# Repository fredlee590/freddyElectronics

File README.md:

freddyElectronics
=================

Repository to keep up with hobbyist electronics projects

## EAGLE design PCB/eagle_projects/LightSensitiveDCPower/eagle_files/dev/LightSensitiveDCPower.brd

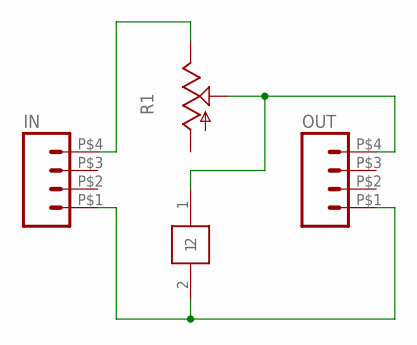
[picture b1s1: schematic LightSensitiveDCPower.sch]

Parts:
IN: M04HORIZ_PTH; SULLIN-1X4_HORIZ
OUT: M04HORIZ_PTH; SULLIN-1X4_HORIZ
PC1: PDV-P8101; PHOTOCELL_CERAMIC
R1: TRIM_US-B25P; B25P

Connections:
unnamed: IN.P$1 (1), OUT.P$1 (1), PC1.2
unnamed: IN.P$4 (4), R1.E
unnamed: OUT.P$4 (4), PC1.1, R1.S

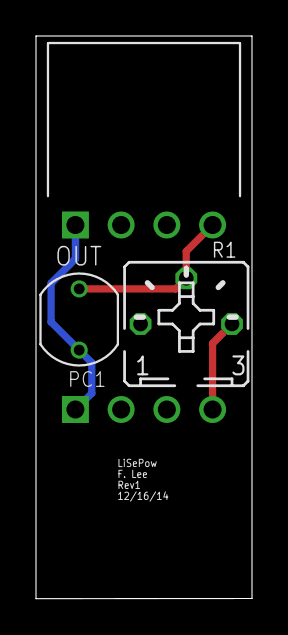
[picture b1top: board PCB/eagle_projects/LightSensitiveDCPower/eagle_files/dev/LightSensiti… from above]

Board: 2 copper layers, 12.0 x 31.3 mm, 4 parts (1 on the bottom side), 3 nets.

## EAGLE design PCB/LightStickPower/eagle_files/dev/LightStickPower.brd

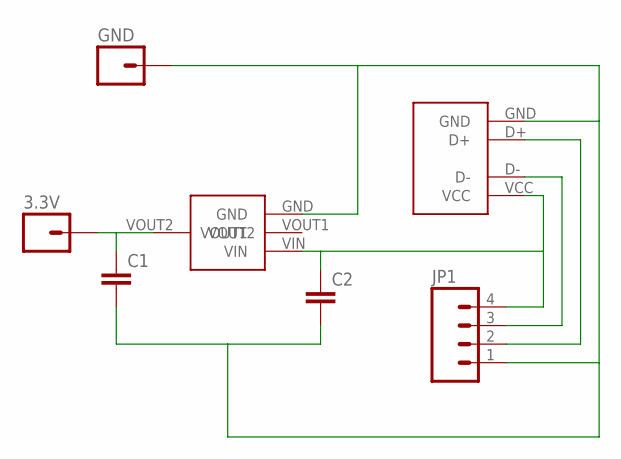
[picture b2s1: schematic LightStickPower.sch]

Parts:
3.3V: M01PTH; 1X01
C1, C2: CAP0805; 0805
GND: M01PTH; 1X01
JP1: M04PTH; 1X04
USB1: USB_A_932
V1: VOLTAGE_REGULATOR_AP2114H; SOT-223

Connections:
unnamed: C2.1, JP1.4, USB1.VCC, V1.VIN
unnamed: JP1.3, USB1.D-
unnamed: JP1.2, USB1.D+
unnamed: C1.2, C2.2, GND.1, JP1.1, USB1.GND, V1.GND
unnamed: 3.3V.1, C1.1, V1.VOUT2

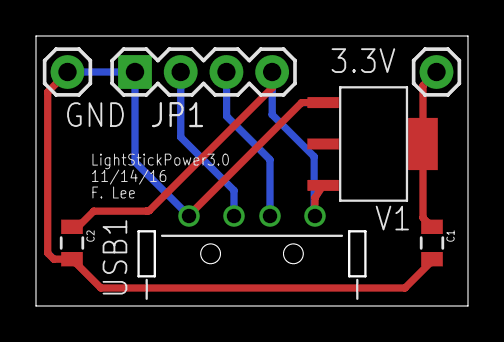
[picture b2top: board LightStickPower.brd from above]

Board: 2 copper layers, 23.9 x 14.9 mm, 7 parts (0 on the bottom side), 5 nets.

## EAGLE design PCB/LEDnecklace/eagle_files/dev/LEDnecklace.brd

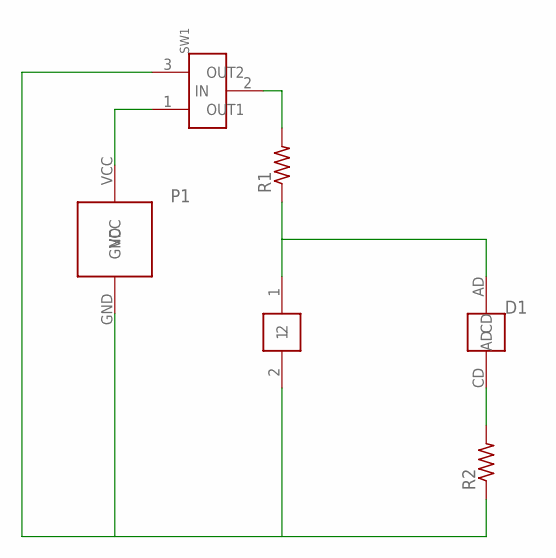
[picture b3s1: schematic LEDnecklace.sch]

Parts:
D1: XLAMP_XBD
P1: BC501SM_BATT_HOLD
PC1: PDV-P8101; PHOTOCELL_CERAMIC
R1, R2: R-US_R0603; R0603
SW1: PCM12SMTR

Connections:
unnamed: R1.2, SW1.2 (IN)
unnamed: P1.GND, PC1.2, R2.1, SW1.3 (OUT2)
unnamed: P1.VCC, SW1.1 (OUT1)
unnamed: D1.AD, PC1.1, R1.1
unnamed: D1.CD, R2.2

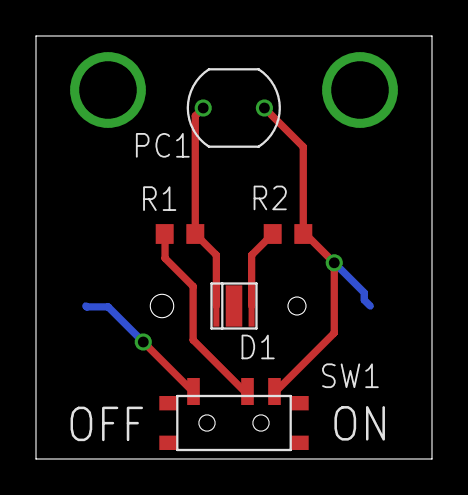
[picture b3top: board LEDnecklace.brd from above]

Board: 2 copper layers, 22.0 x 23.5 mm, 6 parts (1 on the bottom side), 5 nets.

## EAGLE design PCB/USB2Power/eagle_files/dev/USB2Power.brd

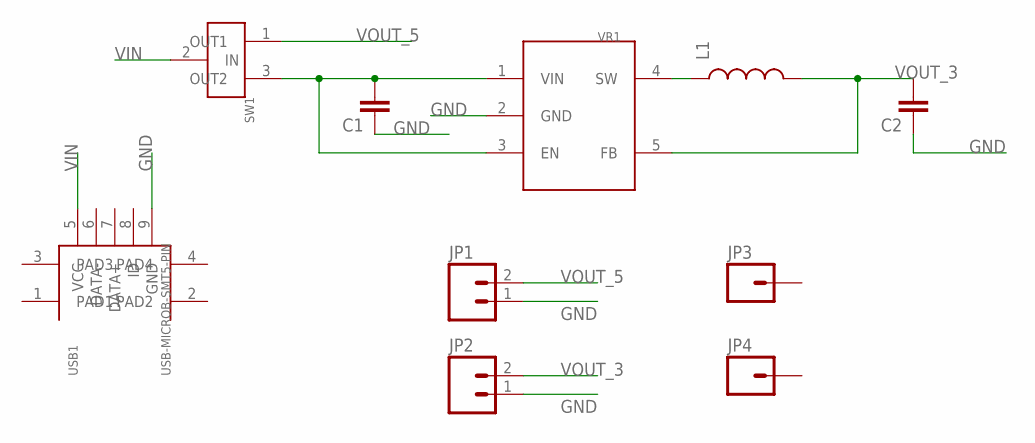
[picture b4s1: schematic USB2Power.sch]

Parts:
C1, C2: CAP0603-CAP; 0603-CAP
JP1, JP2: M02PTH; 1X02
JP3, JP4: M01PTH; 1X01
L1: INDUCTOR30OHM,1.8A; 0603
SW1: PCM12SMTR
USB1: USB-MICROB-SMT5-PIN; USB-MICROB-SMT
VR1: ADP2108; UJ-5_TSOT

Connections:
GND: C1.1, C2.1, JP1.1, JP2.1, JP3.1, JP4.1, USB1.9 (GND), VR1.2 (GND)
unnamed: C1.2, SW1.3 (OUT2), VR1.1 (VIN), VR1.3 (EN)
unnamed: L1.1, VR1.4 (SW)
VIN: SW1.2 (IN), USB1.5 (VCC)
VOUT_3: C2.2, JP2.2, L1.2, VR1.5 (FB)
VOUT_5: JP1.2, SW1.1 (OUT1)

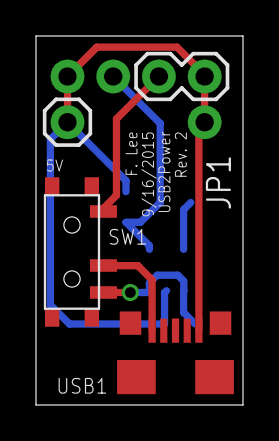
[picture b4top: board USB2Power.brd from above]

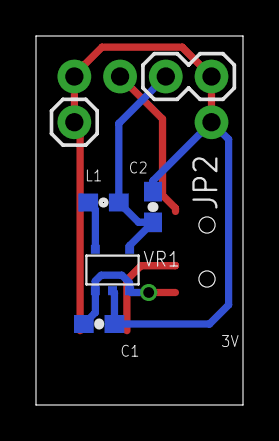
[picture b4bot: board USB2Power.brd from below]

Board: 2 copper layers, 11.5 x 20.5 mm, 10 parts (6 on the bottom side), 6 nets.

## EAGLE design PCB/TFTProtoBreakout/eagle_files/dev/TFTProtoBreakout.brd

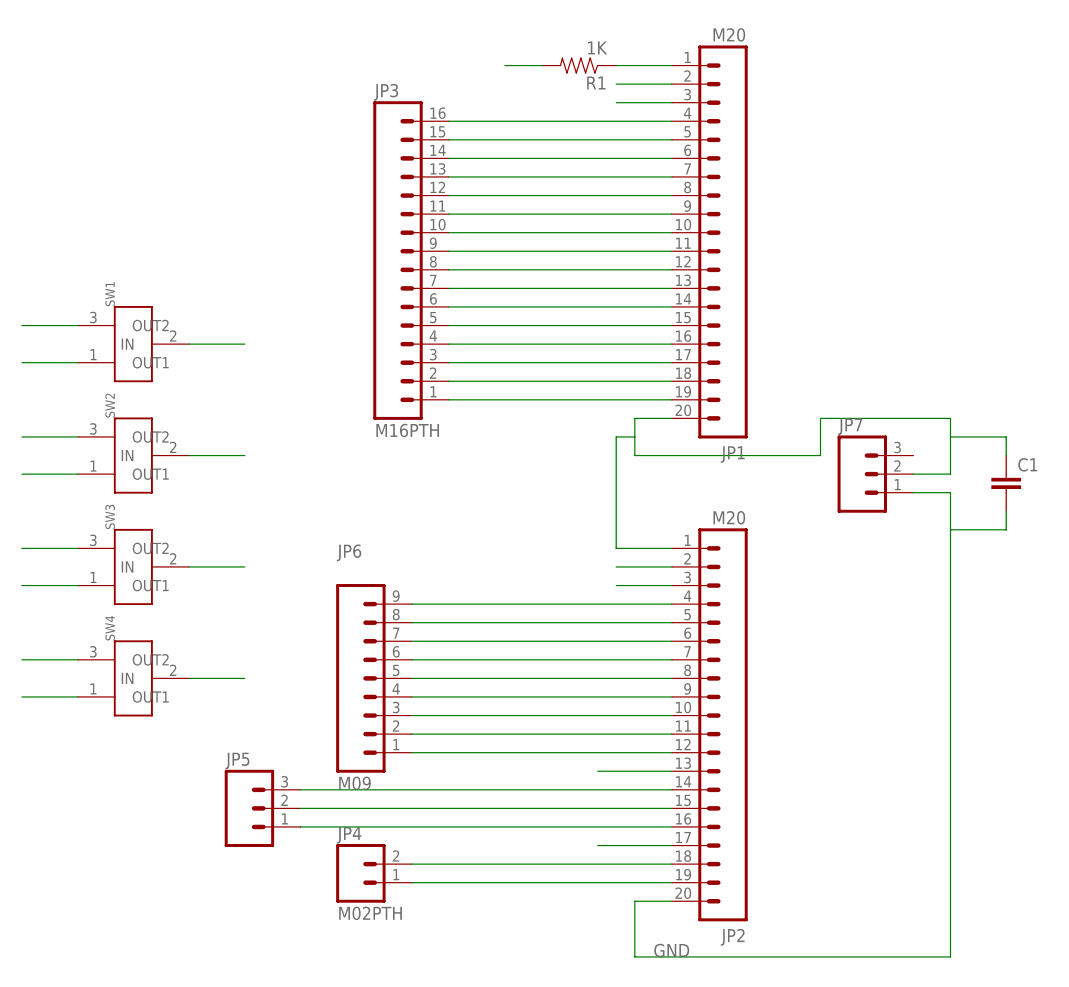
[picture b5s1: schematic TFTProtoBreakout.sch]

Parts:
C1: CAP0805; 0805
JP1, JP2: M20; 1X20
JP3: M16PTH; 1X16
JP4: M02PTH; 1X02
JP5, JP7: M03PTH; 1X03
JP6: M09; 1X09
R1: 1K; 0603-RES
SW1, SW2, SW3, SW4: PCM12SMTR

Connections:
D0: JP1.13, JP3.7
D1: JP2.12, JP6.1
D2: JP1.12, JP3.8
D3: JP2.11, JP6.2
D4: JP1.11, JP3.9
D5: JP2.10, JP6.3
D6: JP1.10, JP3.10
D7: JP2.9, JP6.4
D8: JP1.9, JP3.11
D9: JP2.8, JP6.5
D10: JP1.8, JP3.12
D11: JP2.7, JP6.6
D12: JP1.7, JP3.13
D13: JP2.6, JP6.7
D14: JP1.6, JP3.14
D15: JP2.5, JP6.8
D16: JP1.5, JP3.15
D17: JP2.4, JP6.9
FMARK: JP1.17, JP3.3
GND: C1.2, JP2.13, JP2.17, JP2.20, JP7.1, R1.2, SW1.1 (OUT1), SW2.1 (OUT1), SW3.1 (OUT1), SW4.1 (OUT1)
IM0: JP1.2, SW1.2 (IN)
IM1: JP2.2, SW2.2 (IN)
IM2: JP1.3, SW3.2 (IN)
IM3: JP2.3, SW4.2 (IN)
LEDK: JP1.1, R1.1
NCS: JP2.16, JP5.1
NRD: JP1.15, JP3.5
NRST: JP1.4, JP3.16
NWR_SCL: JP2.15, JP5.2
RS: JP1.16, JP3.4
SDI: JP2.14, JP5.3
SDO: JP1.14, JP3.6
VCC: C1.1, JP1.20, JP2.1, JP7.2, SW1.3 (OUT2), SW2.3 (OUT2), SW3.3 (OUT2), SW4.3 (OUT2)
X+: JP1.18, JP3.2
X-: JP1.19, JP3.1
Y+: JP2.18, JP4.2
Y-: JP2.19, JP4.1

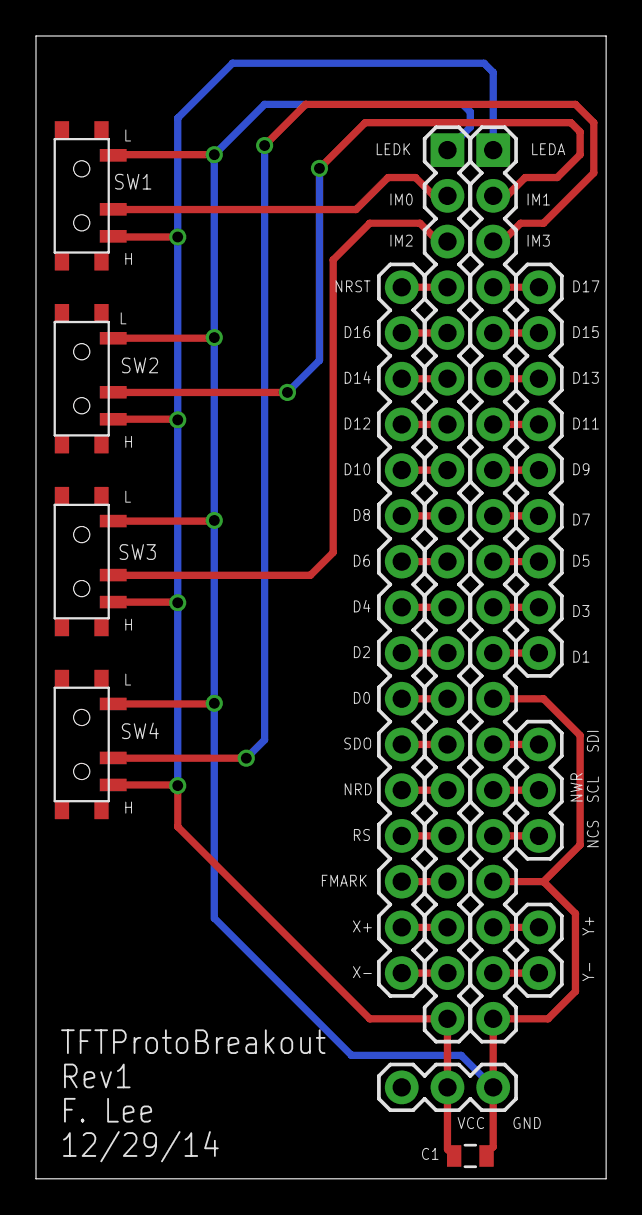
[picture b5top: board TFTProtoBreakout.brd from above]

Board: 2 copper layers, 31.7 x 63.5 mm, 13 parts (1 on the bottom side), 37 nets.

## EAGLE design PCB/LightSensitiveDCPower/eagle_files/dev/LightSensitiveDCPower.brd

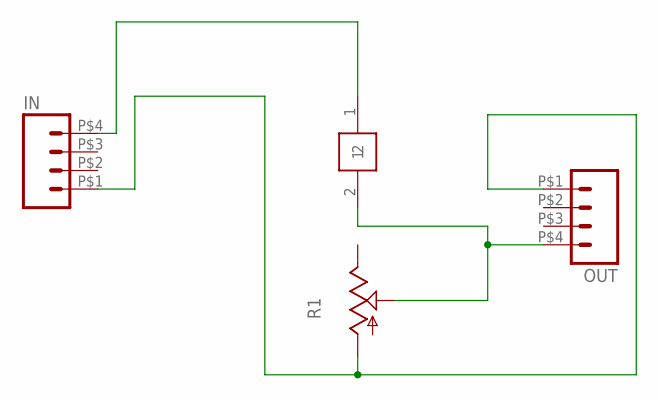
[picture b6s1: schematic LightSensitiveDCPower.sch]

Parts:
IN: M04HORIZ_PTH; SULLIN-1X4_HORIZ
OUT: M04HORIZ_PTH; SULLIN-1X4_HORIZ
PC1: PDV-P8101; PHOTOCELL_CERAMIC
R1: TRIM_US-B25P; B25P

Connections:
unnamed: IN.P$1 (1), OUT.P$1 (1), R1.A
unnamed: IN.P$4 (4), PC1.1
unnamed: OUT.P$4 (4), PC1.2, R1.S

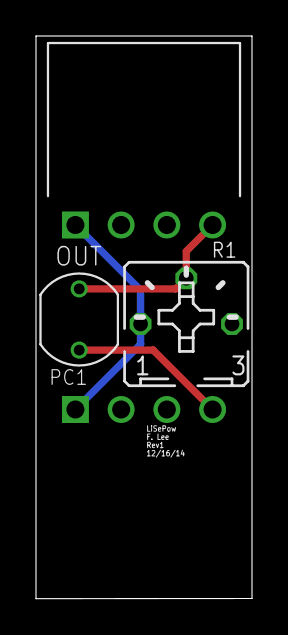
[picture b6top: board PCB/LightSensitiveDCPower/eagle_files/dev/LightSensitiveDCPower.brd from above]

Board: 2 copper layers, 12.0 x 31.3 mm, 4 parts (1 on the bottom side), 3 nets.

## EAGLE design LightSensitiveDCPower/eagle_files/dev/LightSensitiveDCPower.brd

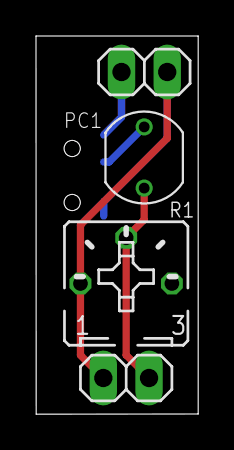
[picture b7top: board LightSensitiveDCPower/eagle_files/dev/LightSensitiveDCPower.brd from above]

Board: 2 copper layers, 9.0 x 21.0 mm, 5 parts (1 on the bottom side), 4 nets.

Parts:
IN: 1X02
OUT: 1X02
PC1: PHOTOCELL_CERAMIC
R1: B25P
SW1: PCM12SMTR

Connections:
unnamed: IN.1, OUT.1, R1.A, SW1.1
unnamed: IN.2, SW1.3
unnamed: PC1.1, SW1.2
unnamed: OUT.2, PC1.2, R1.S

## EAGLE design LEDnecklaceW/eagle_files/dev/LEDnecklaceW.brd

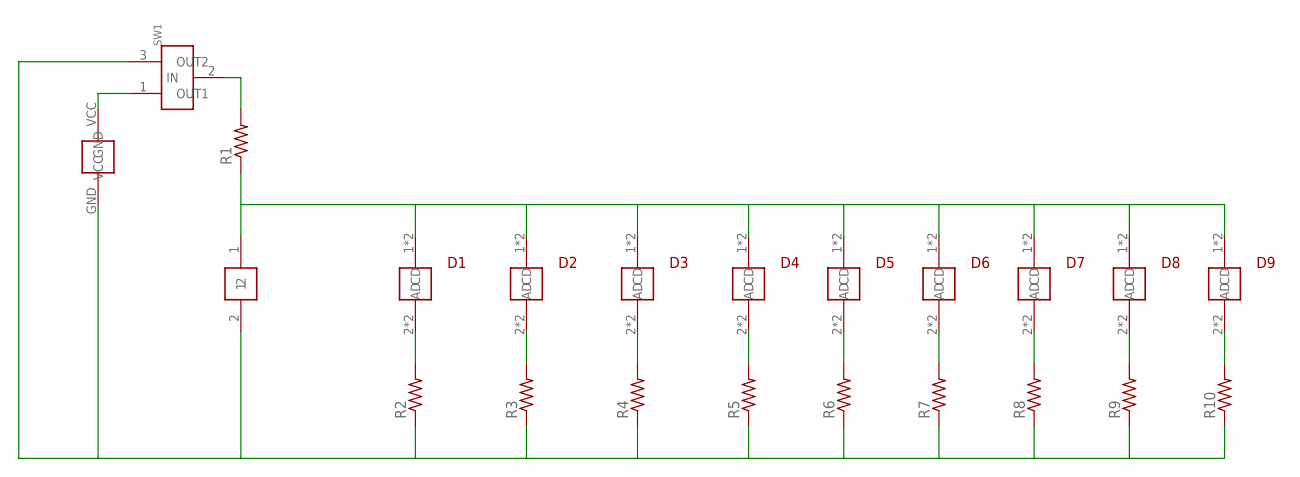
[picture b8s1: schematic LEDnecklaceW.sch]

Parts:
D1, D2, D3, D4, D5, D6, D7, D8, D9: SZA05A0A
P1: BU2032SM-BT-GCT; SMD_BATT_HOLDER_2032
PC1: PDV-P8101; PHOTOCELL_CERAMIC
R1, R2, R3, R4, R5, R6, R7, R8, R9, R10: R-US_R0603; R0603
SW1: PCM12SMTR

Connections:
unnamed: R1.2, SW1.2 (IN)
unnamed: P1.GND, PC1.2, R2.1, R3.1, R4.1, R5.1, R6.1, R7.1, R8.1, R9.1, R10.1, SW1.3 (OUT2)
unnamed: D1.2 (CD), D1.12 (CD), R2.2
unnamed: P1.VCC, SW1.1 (OUT1)
unnamed: D2.2 (CD), D2.12 (CD), R3.2
unnamed: D3.2 (CD), D3.12 (CD), R4.2
unnamed: D4.2 (CD), D4.12 (CD), R5.2
unnamed: D5.2 (CD), D5.12 (CD), R6.2
unnamed: D6.2 (CD), D6.12 (CD), R7.2
unnamed: D7.2 (CD), D7.12 (CD), R8.2
unnamed: D8.2 (CD), D8.12 (CD), R9.2
unnamed: D9.2 (CD), D9.12 (CD), R10.2
unnamed: D1.1 (AD), D1.11 (AD), D2.1 (AD), D2.11 (AD), D3.1 (AD), D3.11 (AD), D4.1 (AD), D4.11 (AD), D5.1 (AD), D5.11 (AD), D6.1 (AD), D6.11 (AD), D7.1 (AD), D7.11 (AD), D8.1 (AD), D8.11 (AD), D9.1 (AD), D9.11 (AD), PC1.1, R1.1

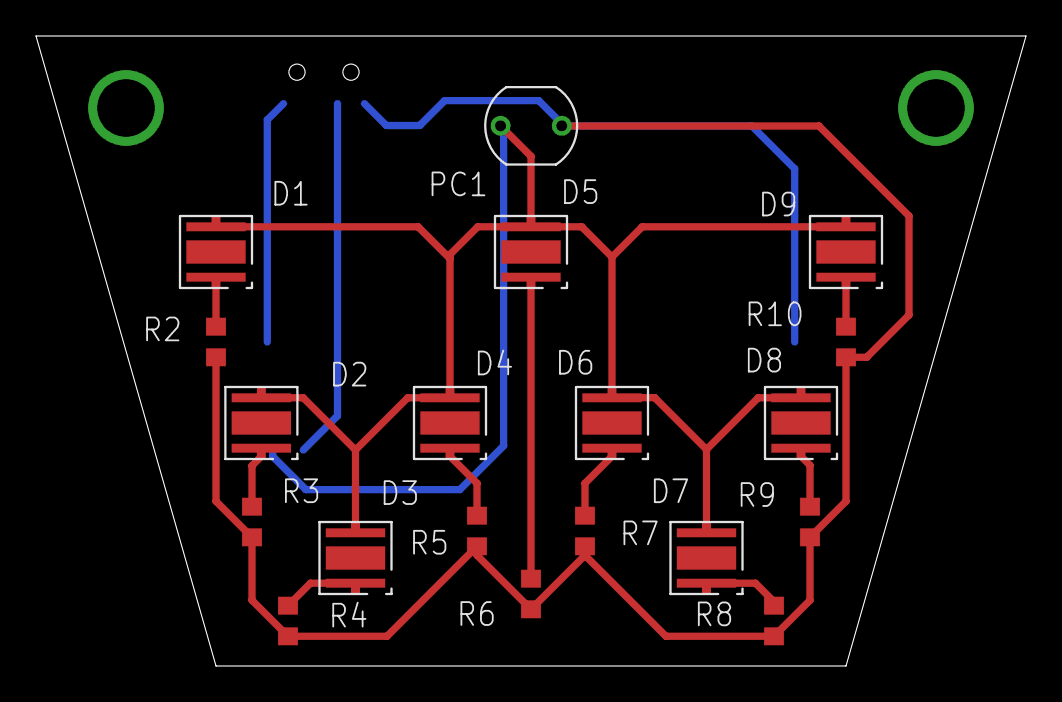
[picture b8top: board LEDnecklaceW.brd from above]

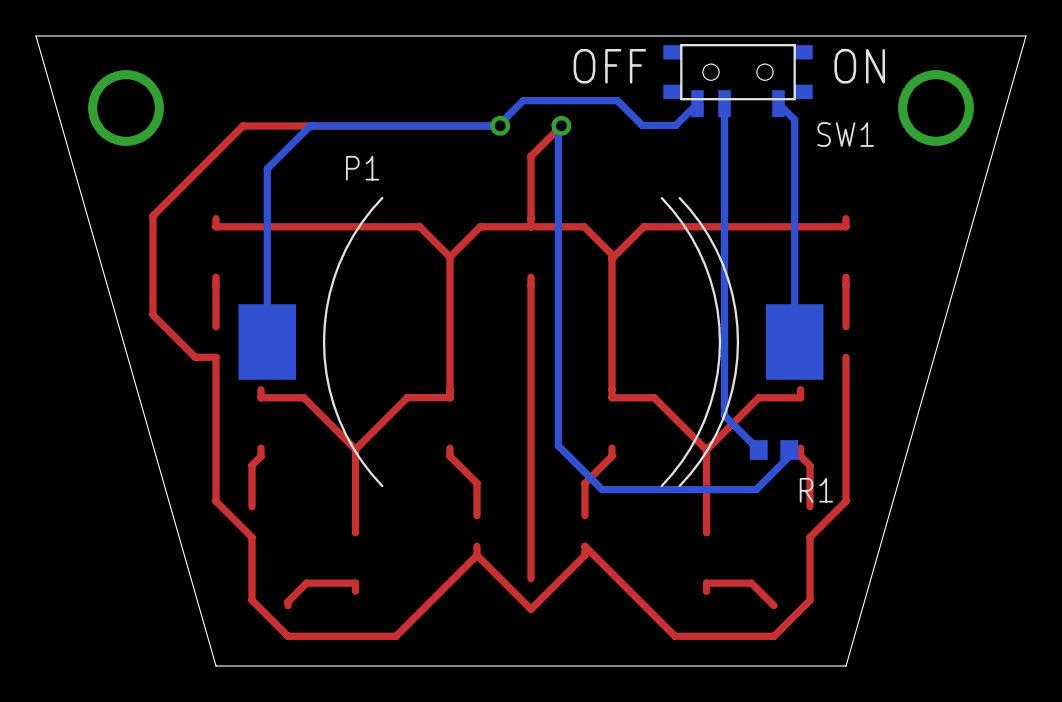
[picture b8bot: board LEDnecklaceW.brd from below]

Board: 2 copper layers, 55.0 x 35.0 mm, 22 parts (3 on the bottom side), 13 nets.

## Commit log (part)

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2013-08-07 new project folder and initial file in the form of a partlist
2013-08-18 add eagle files. checkpoint. have functional set board lay out. attempting to consolidate
2013-08-18 add script file to copy select eagle files (project, schematic, and board) into dev folder
2013-08-18 new file structure to prepare for later projects. copy_eagle modified to correpsond to new files structure.
2013-08-18 copy_eagle added to commit list
2013-08-18 new consolidated mcuPower.brd
2013-08-19 updated eagle project and board and generated gerber files. modified copy_eagle to get output as well
2013-08-26 most complete to date files
2013-08-26 added mcuPower.dri as aperture wheel file and committed associated changes
2013-08-26 added dxf file and edited copy_eagle to copy this as well
2013-08-31 tweaked voltage regulator to remove some silkscreen guide lines that overlap with traces
2013-09-02 packaged eagle_files into zip folder for easy emailing
2013-09-02 moved some files around. better name for eagle_files.zip and more organized location for mcuPower.xls
2013-09-02 deleted mcuPower.xls as part of previous commit
2013-09-02 zip file is now a subset of previous. only production files
2013-09-08 various changes + production files. Reroutes, library footprint changes, and moving pot to front side of board
2013-09-22 added GML file for board outline for Seeedstudio. Modified copy_eagle script to include GML. Peripheral changes to eagle.epf and mcuPower.dri
2013-09-22 Rename zips with production files
2013-09-22 move mcuPower_prod_proto.zip \(renamed\) to mcuPower directory
2013-09-22 Making official the deletion of mcu_prod_proto.zip
2013-10-26 removed label in silkscreen for stabilizing pin
2013-10-27 new production files for OSHPark. also, copy_eagle version to copy those files to the production file folder. board design itself shows flipped coin battery holder
2013-10-27 corrected naming of Gerber for top layer and bottom layer
2013-10-27 adding zip file for OSHPark's specifications
2013-12-23 initial commit of mcuWallPower project: A variation of mcuPower that delivers power to a breadboard from a single coin battery or a micro-B USB cable.
2013-12-24 Added USB mini connector to board along with other components. Todo: Replace USB mini connector with USB micro B connector. Looks like I'll need to make a custom footprint.
2013-12-24 renamed copy_eagle to copy_eagle.sh. More professional convention (?).
2013-12-26 add eagle library to git. contains handful of custom parts.
2013-12-26 mcuWallPower schematic and board updated. Ready for fitting.
2014-01-06 latest project files. using latest footprint for USB-micro-B component.
2014-01-06 initial commit for LED necklace BOM
2014-01-12 generated top and bottom overlay (silkscreens) with PCB info changed from top to bottom silkscreen.
2014-01-12 updated board file to put ID information on the back.
2014-01-19 Renamed BOM_LED_Necklace.xlsx to BOM_LED_Necklace.xls
2014-01-19 Adjust last entry to include single purchase option.
2014-01-20 Final candidate list of LEDs
2014-01-20 update spreadsheet to reflect datasheets.
2014-01-20 upload datasheets thus far.
2014-01-27 copy_eagle.sh assigns project name at the beginning. more versatile for future revision. also creates project folder if not already present.
2014-01-27 initial commit of LEDtestBoard PCB project . Power finalized, switches and LEDs in general place. Set up for one side to hold 4 LEDs and the other to hold a multicolored LED, controlled with 4 switch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
2014-02-02 added two new datasheets to match previous commit of new LEDs (including multicolored LED).
2014-02-02 Formalized decisions on 5 LEDs to use
2014-02-02 Added gull wing LED (already have) to list
2014-02-02 added datasheet for the photocell to use
2014-02-02 Updated BOM spreadsheet for photocell.
2014-02-13 add test to test merge one file
2014-02-13 more test.txt
2014-02-15 Add datasheet for amber version of last LED
2014-02-15 Update BOM to use all amber LEDs. Also narrow down search to two
2014-02-17 Updated LEDtestBoard dev files. Ready to begin pad check and routing.
2014-02-21 Placed components in approximately precise locations. Ready to begin routing.
2014-02-21 Modified LED footprints to have more visible special corner and to display names.
2014-02-26 All routed.
2014-03-06 New design rules and all visible. And some other stuff. Project files.
2014-03-06 Add production files. Getting ready to request.
2014-03-09 Adjusted part labels in board design and generated output accordingly.
2014-03-10 All layers visible
2014-03-10 Move components around to make USB micro B power source more stable. Coin battery upright.
2014-03-10 Output files of mcuWallPower version 2. Switch sources with output positions.
2014-03-10 Move text under trace. Just in case heating concern.
2014-04-05 Remove dxf file for mcuWallPower. Not needed for OSHPark.
2014-04-05 LEDnecklaceW board routed.
2014-04-05 LEDnecklaceW board and schematic updated to show component names for photocell and battery.
2014-04-05 Updated freddyLibr.lbr - Show names of photocell and battery case.
2014-04-05 Moved some names around.
2014-04-05 First run of Eagle production files for OSHPark.
2014-04-06 Added switch to board and schematic. Also added output production files corresponding to these changes.
2014-04-06 Added labels for ON and OFF position. board and changed production files.
2014-04-10 updated eagle production files for final submission
2014-07-26 Add GML (outline) and TXT (Drill Drawing) to match SeeedStudio requirements.
2014-08-19 Add BOM for convenient part ordering
2014-08-19 Added part spaces.
2014-09-20 Create new project LightSensitiveDCPower
2014-09-20 Re-place parts with readjusted text and new labels
2014-09-20 Further rearranging and resizing.
2014-09-20 Corrected Pot miswiring. Further rearranging and resizing. I think this is it.
2014-09-20 Restructuring of project file. Apparently.
2014-09-20 Add LightSensitiveDCPower production files.
2014-09-25 Minor changes due to regeneration of production files.
2014-09-25 Elongate board to save for wiidth. Check point.
2014-11-24 Move all PCB files to new PCB directory. Update Bill of Materials for LEDnecklaceW.
2014-12-02 New horizontal female header scheme for Light Sensitive DC power with dimensions adjusted accordingly.
2014-12-03 Rearranged components so that board is less long.
2014-12-03 Routed and produced production files.
2014-12-03 Yet another tweaking of component postiions.
2014-12-13 Removed switch. Intended use case turned out to be out of rating.
2014-12-13 Initial check in of BeagleBone Black robotic stuff.
2014-12-15 Changed board label to Rev1 and today.
2014-12-15 Bring PCB label into soldermask
2014-12-15 Files generated by new CAM file.
2014-12-28 Added first cut of trace routing to board design. A bit messy, but functional.
2014-12-28 Modified to be a bit more clean.
2014-12-28 Added pin labels and rerouted to work around these a bit more cleanly. Also included note about switch todo.
2014-12-29 Minor changes to eagle project file.
2014-12-29 Laid switches on one face abreast and routed.
2014-12-29 Finalize routing to be more clean. Add keyhole for Power connections and Add labels.
2014-12-30 Rename label to TFTProtoBreakout.
2014-12-30 Eagle project file changed after save. Different position?
2015-01-11 LiSensiPow actually works now
2015-08-18 Add 5V to 3.3V voltage regulator to freddy library.
2015-08-18 Add schematic and board file for USB2Power project. First cut of component placement.
2015-08-21 USB2Power board components placed and ready for routing.
2015-08-21 Slightly tweak borders of USB2Power.
2015-08-21 All connected up. Also added ground for the other two header pins as opposed to NC. Made connections a little better. Some known DRC failures.
2015-08-21 Add OSHPark's design rules file.
2015-08-25 Resolve DRC conflicts with USB2Power.brd
2015-08-25 Add Board descriptor.
2015-08-26 First generation of production files.
2015-09-15 Add separate headers for 5V and 3V power outputs. Joint header + inductor may have been causing problems.
2015-09-25 Add basic serial PIC project as a starting point for projects with debugging.
2015-09-25 Move basic project to platform specific folder 18F24J50
2015-09-26 Turn off watchdog timer.
2015-09-26 Remove build files.
2015-09-29 Include starting position of RF transmitter and receiver.
2015-10-29 Snapshot of RFtransmitter with basic read from RF module.
2015-11-05 Move project to Git directory.
2015-11-05 Basic SPI scaffolding.
2015-11-05 Snapshot before major surgery.
2015-11-05 Adjusted readReg and writeReg functions to return success (0) or error code (-1).
2015-11-17 Compress function to get STATUS register and unify function to write SPI.
2015-11-18 Fix up readStatus function and add write checks in debugging capacity.
2015-11-18 Miscellaneous clean up via more macros. First attempt to send a packet.
2015-11-18 Minor tweaks to process to try to get TX interrupt to fire. Command for write that doesn't require an ACK. More Nops. Disable sending external interrupt notification.
2015-11-25 Add quintessential blinking project. Useful for experimenting with delays.
2015-11-25 Refactor config write function to be more direct.
2015-12-04 Further attempts to transmit packet. Move configuration around, add function to flush TX FIFO, extra checks.
2015-12-09 Refactor function structure to match example code.
2016-03-23 First cut of LED test necklace's Eagle dev files.
2016-03-24 Add Digikey order for LEDs etc.
2016-03-25 Add new generation of datasheets.
2016-03-25 Rename datasheets to make them easier to identify.
2016-03-28 Add new LED XLamp XB D to library and simple breakout board.
2016-03-30 Develop version of LEDnecklace with XLampXBD and smaller coin cell (type 2016).
2016-03-30 Price analysis for LEDnecklace.
2016-05-18 Change border around LED. Hopefully more visible.
2016-06-28 Add Arduino projects with first submission. Light sock design document.
2016-07-06 Add 3D printing directory along with first project: RouterRack.
2016-07-06 Updated FCStd files. Somehow.
2016-08-12 Initial check-in of LightStickPower and associated updated freddyLibr.lbr
2016-08-15 Finalize LightStickPower.
2016-08-19 Initial commit of some test code (midpoint to production code) and hardware design documentation.
2016-08-23 Add drawing for core of LightStick. To be laser cut from polycarbonate sheet.
2016-08-23 Update routerRack development and production files.
2016-08-23 Initial check in of Light Stick block diagram.
2016-08-24 Widen USB micro slot. Developer and production file.
2016-08-25 Initial check in of short router rack side.
2016-08-25 Add crossbar for stability.
2016-08-25 Adjusted line segment names.
2016-08-26 Add back stabilizer piece.
2016-08-29 Adjust core drawing to have holes and smaller dimensions.
2016-09-20 Update LightStickPower with more precise borders and thinner traces where appropriate.
2016-09-20 Add holes to allow for pins on prototype Teensy and accelerometer.
2016-09-20 Adjust short router rack pieces to be just a little bit bigger. Bet I got it this time.
2016-09-20 Updated date on LightStickPower.
2016-09-20 Narrow board to fit in tube.
2016-10-04 Updated core.
2016-10-04 Adjust USB micro B head of LightStickPower.
2016-10-08 Removed extraneous line.
2016-11-15 Updated Light stick power to use cabled USB-micro-B plug. Also commit properly pathed copy_eagle. Getting annoying.
2016-11-28 Add crystalPerch, a stand for crystal acquired in Japan.
2016-11-28 Reset view for crystalPerch. Remove extraneous file.
2016-11-28 Remove extraneous sketch.
2016-12-26 Add accessory holes. Power and photoresistor.
2016-12-29 Created and populated eagle_projects directory with previous projects.
2016-12-29 Streamline copy_eagle.sh to use unified variables.
2016-12-29 Add template for bill of materials for better planning going forward.
2016-12-29 Initial check in of project groundwork for LightStickControl board.
2017-01-02 Initial check in of CrystalPerch Arduino sketch.
2017-01-18 Widen holes and make taller.
2017-02-21 Restructure eagle_libs to be more flat. Initial commit of empty library for Adafruit Arduino Trinket.
2017-05-10 Update custom Eagle libraries.

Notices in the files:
parts and their libraries:
SparkFun-Connectors: Licensing: CC v3.0 Share-Alike You are welcome to use this library for commercial purposes.
SparkFun-Connectors: Licensing: Creative Commons ShareAlike 4.0 International - https://creativecommons.org/licenses/by-sa/4.0
